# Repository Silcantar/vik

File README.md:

# VIK

> **Warning**
> This is a work in progress. It has been tested to be functional, but please consult **sadekbaroudi** in the **#vik** channel of the [fingerpunch discord server](https://fingerpunch.xyz/discord) if you'd like to design a keyboard or module.

> **Note**
> **To see the list of known supported keyboards and modules, go to [this section](#known-list-of-vik-certifications) at the bottom of the readme**

> **Note**
> Please be aware that for keyboard pcbs, VIK assumes that it's running at 3.3v logic levels. This is easily achieved by using a RP2040. If you are using a 5v controller, it is the keyboard's responsibility to level shift before going to the VIK module. See the [Microcontroller selection](#microcontroller-selection) section below

## License

**The licensing for VIK works as follows:**
The main `LICENSE.md` in the git repository root directory applies to the whole repo, except where there is a `LICENSE.md` in the sub-folder. In that case, that `LICENSE.md` is then applied recursively until there is another `LICENSE.md` in any of its subdirectories (if any).

## Overview

VIK is a standard for a data interface between printed circuit boards. It is intended to provide modularity between a mechanical keyboard pcb and additional features. The main pcb can have a controller and a switch matrix, while the modules can provide additional features.

The standard specifies the following:
1. The type of connector
2. The signals mapped to each pin on the connector
3. The type of cable
4. (optional) The size of the module pcb and mounting hole locations
5. Inclusion of the VIK logo on the PCB

> **Note**
> Adding support for VIK is as simple as adding a symbol and footprint, provided in this repository, followed by some basic wiring. If you want to jump straight to the guide to do this using Kicad, go to [Implementation with Kicad](#implementation-with-kicad)

## Renders

Keyboard with VIK certification using the keyboard footprint

Module with VIK certification using the module footprint

### What value does this bring?

#### Consoldiates efforts for feature design

In a community full of talented people doing lots of innovation, we are seeing a plethora of new options for keyboard layout configurations, features, etc. With all this innovation, we're doing very little to share our efforts.

For example, if one person invests in adding support for a trackball with a scroll wheel, others have to identify how to do that, and add support for their keyboard design.

#### Ease of upgrades

With VIK support, upgrading your features is as simple as getting a new VIK module, and swapping it out.

Let's say you built a keyboard with an integrated trackpad, and you love it. Months after setting it up, you realize that you'd love to have a trackball and haptic feedback. Now you need to design a new pcb (or find someone who has) with the features you'd like. Most people don't know how, or don't want to put forth this effort, so they will settle for their current configuration. With much less effort, you can create a new VIK module, assemble it, and connect to your existing keyboard.

#### One feature for many keyboard layouts

One of the biggest challengs I find, is that a keyboard may have some really excellent features, but I really don't like the key layout. In that case, I won't be interested in the keyboard, despite wanting the features.

Provided that keyboard designers adopt the VIK standard on the main keyboard pcb, the modules are usable on any of those keyboards. So, you can design or find a keyboard that has your preferred layout, and then add the features that you like. True customizability for the exact keyboard you want to use.

## Specifications

There are two things that must be implemented for this to be successful. The keyboard pcb must support the VIK interface, and the module pcb must support the VIK interface

### Connector

The required connector is a FPC 12 pin 0.5mm pitch connector. It should be available on both the keyboard pcb and the module pcb.

#### JLCPCB part selection tips

I've received feedback that the recommended part number `C479750` for the fpc connector (`vik-{keyboard|module}-connector-horizontal`) is frequently out of stock. Fortunately, there are many equivalent parts that line up identically to this one.

To find an equivalent, I generally just search for "12p 0.5mm fpc clamshell". Then I pick one that looks identical to `C479750`. During PCBA part placement, go into 3D mode and adjust the view to make sure the pads line up nicely with the connectors. An example of an alternative part number is `C2906115`.

### Cable

The cable should be a 12 pin 0.5mm pitch FPC Type A cable (leads are exposed on the same side).

The specs below state that you must invert the connector pin order between the keyboard and the module, which means Type A is required.

### Interface

The interface includes the following signals:
* 3.3V
* GND
* SDA
* SCL
* RGB Data Out
* Vout
* Digital/Analog GPIO/CS 1
* MOSI
* Digital/Analog GPIO/CS 2
* Digital/Analog GPIO/CS 3
* MISO
* SCLK

The order specified above is the order they should be used on the FPC connector on the **keyboard side**, pins 1 through 12. For the module pcbs, they should be inverted, since the cable will automatically invert the order when connected. If you use the VIK Kicad symbols and footprints, this is managed for you. See the [Implementation with Kicad](#implementation-with-Kicad) section below

### VIK logo

So long as you adhere to the specs above, you can consider your keyboard pcb or module VIK enabled. The last thing you do before publishing or manufacturing your PCB is to include the VIK logo.

There are a collection of logos you can use in the kicad/vik.pretty directory of this repository, all prefixed with `vik-logo`. For instance, you could take the pre-made kicad footprints and include them on your pcb. If you aren't using kicad, there is a dxf and svg you can use as well.

## Module PCB shape and mounting

This is optional, but highly recommended. By adhereing to a standard size and mounting, this will allow others to design keyboard pcbs and/or cases that will support mounting a variety of modules.

There are two specs, a small and large pcb.

**All mounting holes should fit M2 screws**

### Small PCB

Size: less than 25mm by 42mm

Mounting: 2 mounting holes

### Large PCB

Size: less than 65mm by 65mm

Mounting: 4 mounting holes

The mounting holes should 44.5mm apart in a square, centered around the center of the pcb. Alternatively, you can place these mounting holes evenly distributed around a 63mm circle, also centered around the center of the pcb.

### Module mounting Kicad footprints

There are two mounting footprints, found in the vik.pretty footprints folder:
* vik-module-mounting-small
* vik-module-mounting-large

You can use these for one of two purposes:
1) When creating a module, use the footprint to ensure that your module pcb has the correct mounting locations
2) When creating a keyboard, use the footprint to position where you'd like to mount a module pcb

You can use the Mounting Hole symbol in the schematic, and associate one of the footprints as shown below:

## Implementation with Kicad

Given Kicad's popularity, I've made it (hopefully) very convenient to implement VIK on the keyboard and module side.

### Add symbols and footprints to your Kicad project

1. Clone this repository to your local machine
2. Add the VIK symbol library your project
3. Add the VIK footprint library to your project

Please note that the path in the screenshots won't be the same as yours. It should be:
`{PATH TO CLONE OF THIS REPO}/kicad/vik.kicad_sym`
and
`{PATH TO CLONE OF THIS REPO}/kicad/vik.pretty`

### Kicad keyboard connector

1. Add a new symbol in the schematic, and select the `vik-keyboard-connector`
2. Connect all the signals as specified
3. Associate with the type of footprint you'd like to use (all of the VIK examples use the horizontal connector footprint). Given you are making a keyboard connector, be sure to use the ones that have the word keyboard in them. See the image below for an example.
4. Update your PCB from the schematic and wire it up!

#### Adding the keyboard connector symbol

#### Assigning the keyboard connector footprint

#### Example schematic for keyboard connector

#### Example wiring for keyboard connector

### Kicad module connector

1. Add a new symbol in the schematic, and select the `vik-module-connector`
2. Connect all the signals as specified
3. Associate with the type of footprint you'd like to use (all of the VIK examples use the horizontal connector footprint). Given you are making a module connector, be sure to use the ones that have the word module in them. See the image below for an example.
4. Update your PCB from the schematic and wire it up!

#### Adding the module connector symbol

#### Assigning the module connector footprint

#### Example schematic for module connector

#### Example wiring for module connector

## Schematic design guide

Assuming you already have the VIK symbols and footprints included in your schematic, you will need to wire them according to the specs. Let's walk through each signal, and review how to wire. I'll break this into two parts, one for the keyboard design, and one for the module design.

### Keyboard schematic guide

First and foremost, it's very important that the keyboard have everything set up correctly. Given it's the one supplying the signals to the module, you want to be fully compatible with as many modules as possible.

Here is each signal, and an overview of how to wire it.

**3.3V**

This one is fairly straight forward in the sense that you just need to supply 3.3v. That said, there are controllers out there that do not include it natively. Please review the [Microcontroller selection](#Microcontroller-selection) section below for details.

On wireless microcontrollers, this should be connected directly to BAT+ or to the output of a 3.3V voltage regulator. Do not connect it to the switchable VCC pin (on Nice!Nano or nRFmicro) or to VUSB (on Seeed XIAO nRF52840).

**GND**

Connect ground to this pin.

**SDA**

Microcontrollers usually have more than one set of I2C signals. On dev boards like the [Helios](https://github.com/0xCB-dev/0xCB-Helios) or [Elite-Pi](https://docs.keeb.io/elite-pi-guide), it's as simple as wiring the SDA pin to the corresponding SDA pin on the VIK connector.

nRF52840-based controllers like Nice!Nano, nRFmicro, Seeed XIAO nRF52840, and others have both high- and low-frequency IO pins. SPI and I2C pins should be located *only* on high-frequency pins.

**SCL**

This is the exact same as described for SDA, but using SCL instead.

**RGB Data Out**

If you don't have RGB leds on your keyboard, this can be any digital GPIO. Just pick any data signal, and route it to the RGB pin on the VIK connector.

If you are using RGB leds, you'll want to do two things:
1. Wire the data out from the last LED to the RGB pin on the VIK connector
2. Connect from the controller LED data pin to the VIK connector, but put an open jumper in the middle. The nice thing about this is that it allows the end user to still use the LED feature on a module without necessarily having the LEDs assembled on their keyboard.

**Vout**

`Vout` is a 5 or 3.3 volt power pin intended for supplying higher-power-consumption components like LEDs or screens.

For wired keyboards, `Vout` should usually be connected to the raw 5V provided by the USB connection. If you are using an RP2040 controller board, be aware that the `VCC` pin is 3.3V. For 5V, connect to the `RAW` or `VBUS` output of the controller. On all RP2040-based controllers that I'm aware of as of this writing, this is the top right pin (please double check this before you wire it up).

For example, on the elite-pi:

Connecting `Vout` is a bit more complicated for battery-powered wireless keyboards. Since most LiPo batteries only provide around 3.7 volts, these keyboards only have 5-volt power available when plugged in. Depending on the microcontroller board and battery you are using, you have several options. The microcontroller board determines the type of power-saving options available. However, if you have a large battery power-saving might not be necessary to achieve acceptable battery life.

- **Nice!Nano, nRFmicro, or similar**
    - For lower power consumption: these boards provide a switchable power output (`VCC`). `Vout` may be connected to this if you want to be able to switch off high-power components.

- **Seeed XIAO nRF52840 or similar**
    - For lower power consumption: `VUSB` is only powered on when the keyboard is plugged in via USB. High-power components will be powered off when USB is unplugged.

- **Lemon Wireless**
    - Connect `Vout` to `VRGB`.

- **Integrated or other microcontrollers**
    - You will have to investigate what options are available.

- **For any microcontroller**
    - For higher power consumption: connect `Vout` to `RAW` or `BAT+`. High-power components will be powered on whenever the keyboard power switch is on. Don't go this route on a keyboard that lacks a power switch.
    - You may integrate a power cutoff circuit into the keyboard PCB. See [nRFmicro](https://github.com/joric/nrfmicro) or [Nice!Nano](https://nicekeyboards.com/docs/nice-nano/pinout-schematic) schematics for examples.
    - If you don't expect your keyboard to need high-power modules, you may leave `Vout` disconnected. Be aware that this limits the options of your users however.

**Digital/Analog GPIO 1/SPI CS1**

Similar to the `RGB Data Out`, you can select any pin, but it should support both digital and analog. Below is an example of the Elite-Pi, highlighting its pins that support both.

This pin may also be used by modules for selecting an SPI device.

**MOSI**

Similar to I2C, SPI has predefined locations on most controllers. If doing an integrated controller, please refer to the datasheet to determine the correct pins.

That said, on dev controllers like the [Helios](https://github.com/0xCB-dev/0xCB-Helios) or [Elite-Pi](https://docs.keeb.io/elite-pi-guide), they are standard locations. See the image below. You can wire the 4 SPI pins as shown.

nRF52840-based controllers like Nice!Nano, nRFmicro, Seeed XIAO nRF52840, and others have both high- and low-frequency IO pins. SPI and I2C pins should be located *only* on high-frequency pins.

**Digital/Analog GPIO 2/SPI CS2**

Same as `Digital/Analog GPIO 1`, but this should be a second independent GPIO or CS of the same specifications.

**Digital/Analog GPIO 3/SPI CS3**

Same as `Digital/Analog GPIO 1`, but this should be a third independent GPIO or CS of the same specifications.

**MISO**

No additional info beyond the `MOSI` section above. Same course of action, but for the MISO signal.

**SCLK**

No additional info beyond the `MOSI` section above. Same course of action, but for the SCLK signal.

### Module schematic guide

There aren't any major considerations for the schematic for the module. Everything on the connector is an input, so you can choose what to do with them.

That said, please note that using the I2C or SPI pins for anything **other than I2C or SPI** will break on keyboards that use those signals on the main board. So, please avoid doing so if you care about maximizing compatibility.

## Design guidelines and recommendations

### Reference designs

For the keyboard side, I created a keyboard called [vulpes minora](http://github.com/sadekbaroudi/vulpes-minora). This keyboard has been manufactured and tested to work with VIK modules.

For the module side, please see the pcb directory in this repository. Each subdirectory within it has a module that you can review to see how these are implemented.

### I2C guidelines

#### Keyboard pcb

As mentioned above, the responsibility of using pull up resistors is on the VIK modules. This may cause challenges for a few reasons. You may want (or need) to use I2C on the main keyboard PCB, which means you need to use pull up resistors. If this is the case, please provide instructions to inform the users that when using VIK modules, they will need to remove (or not place) the pull up resistor on the keyboard.

#### Module pcb

When designing a module, please ensure that you include pull up resistors, since the guidelines state that the keyboard pcb is not responsible for it.

### Microcontroller selection

If you are designing a keyboard pcb that uses a dev board as a controller (e.g. pro micro, elite-c, stemcell, etc), you should consider that the VIK specs calls for 3.3V and 5V. Given these controllers operate on 5V and don't provide 3.3V, you won't be able to use them for VIK compatibility without additonal circuitry to convert 5V to 3.3V.

**As described at the top of the README in the note, the keyboard pcb should run at at 3.3v logic levels. The simplest option is to use a RP2040 based development board. For integrated controllers, either use a controller that already runs at 3.3v logic, or level shift the GPIO before going into the VIK connector.**

Some options include:
1. Support only RP2040 based controllers (e.g. splinky, elite-pi, helios), where VCC is 3.3V, and the RAW pin provides 5V
2. Support other 5V controllers, and use something like an LDO to convert 5V to 3.3V for the VIK 3.3V signal and GPIO signals
3. Anything you want, as long as you can provide 5V and 3.3V (both power and 3.3v gpio logic levels)

The vulpes minora is an example of point number 1 above.

## VIK certification

In order to be VIK certified, you should be compliant with everything above, and have your keyboard or module reviewed. Upon review, the reviewer will make a card for your pcb, as explained below.

### VIK keyboard certification card

#### Descriptions

* **FPC connector:** has the correct FPC connector with the right pinout, and is wired to specificaton. See the connectors in the kicad/vik.pretty directory
* **Breakout pins:** includes breakout pins using the [VIK breakout pin footprint](https://github.com/sadekbaroudi/vik/blob/master/kicad/vik.pretty/vik-keyboard-throughole.kicad_mod), or has through holes for all the signals. This allows easy access to all the signals. Also, the footprint is compatible with a [hand solderable FPC breakout board](https://www.amazon.com/uxcell-Converter-Couple-Extend-Adapter/dp/B07RVD1J1K).
* **Supplies: Vout** supplies Vout (5V or VBAT)
* **Supplies: SPI** supplies SPI signals, including MISO, MOSI, SCLK, and at least one GPIO/CS
* **Supplies: I2C:** supplies I2C, including SDA and SCL
* **I2C on main PCB:** Does the main PCB use any I2C already. Valid responses are `yes` or `no`. If this is true, the `I2C pull ups` field must have a value
* **I2C pull ups:** I2C pull up resistor value, :x: if no pull ups on the main pcb, or resistor value if present
* **Supplies: RGB:** supplies RGB data out
* **Supplies: Extra GPIO/CS 1:** supplies the extra GPIO, response will be one of: (**:x: | Digital Only | Analog/Digital**)
* **Supplies: Extra GPIO/CS 2:** supplies the extra GPIO, response will be one of: (**:x: | Digital Only | Analog/Digital**)
* **Supplies: Extra GPIO/CS 3:** supplies the extra GPIO, response will be one of: (**:x: | Digital Only | Analog/Digital**)

#### Keyboard sample cards

Example of a failing card:

| Category                    | Classification          | Response           |
| --------------------------- | ----------------------- | ------------------ |
| FPC connector               | Required                | :heavy_check_mark: |
| Breakout pins               | Recommended             | :x:                |
| Supplies: Vout              | Recommended             | :x:                |
| Supplies: SPI               | Required                | :heavy_check_mark: |
| Supplies: I2C               | Required                | :heavy_check_mark: |
| I2C on main PCB             | Discouraged             | yes                |
| I2C pull ups                | Informative             | 2.2kΩ              |
| Supplies: RGB               | Required                | :x:                |
| Supplies: Extra GPIO/CS 1   | Required                | :x:                |
| Supplies: Extra GPIO/CS 2   | Required                | :x:                |
| Supplies: Extra GPIO/CS 3   | Required                | :x:                |

A "perfect" keyboard card would look like this:

| Category                    | Classification          | Response           |
| --------------------------- | ----------------------- | ------------------ |
| FPC connector               | Required                | :heavy_check_mark: |
| Breakout pins               | Recommended             | :heavy_check_mark: |
| Supplies: Vout              | Recommended             | :heavy_check_mark: |
| Supplies: SPI               | Required                | :heavy_check_mark: |
| Supplies: I2C               | Required                | :heavy_check_mark: |
| I2C on main PCB             | Discouraged             | no                 |
| I2C pull ups                | Informative             | N/A                |
| Supplies: RGB               | Required                | :heavy_check_mark: |
| Supplies: Extra GPIO/CS 1   | Required                | Analog/Digital     |
| Supplies: Extra GPIO/CS 2   | Required                | Analog/Digital     |
| Supplies: Extra GPIO/CS 3   | Required                | Analog/Digital     |

### VIK module certification card

#### Descriptions

* **FPC connector:** has the correct FPC connector with the right pinout, and is wired to specificaton. See the connectors in the kicad/vik.pretty directory
* **Breakout pins:** includes breakout pins using the [VIK breakout pin footprint](https://github.com/sadekbaroudi/vik/blob/master/kicad/vik.pretty/vik-keyboard-throughole.kicad_mod), or has through holes for all the signals. This allows easy access to all the signals. Also, the footprint is compatible with a [hand solderable FPC breakout board](https://www.amazon.com/uxcell-Converter-Couple-Extend-Adapter/dp/B07RVD1J1K).
* **Uses: Vout** the module uses the Vout pin to power components.
* **Uses: SPI:** the module is utilizing SPI
* **SPI used for SPI only:** if you are using any of the SPI gpio for any purpose other than SPI, this will remain unchecked. This means that keyboard pcbs that use SPI will be incompatible with this module.
* **Uses: I2C:**
* **I2C used for I2C only:** if you are using any of the I2C gpio for any purpose other than I2C, this will remain unchecked. This means that keyboard pcbs that use I2C will be incompatible with this module.
* **I2C pull ups:** I2C pull up resistor value, if applicable. These are only required if I2C is being used on the module.
* **Uses: RGB:** uses RGB data out
* **Uses: Extra GPIO 1:** uses the extra GPIO/CS, response will be one of: (**:x: | Digital Only | Analog/Digital | CS**)
* **Uses: Extra GPIO 2:** uses the extra GPIO/CS, response will be one of: (**:x: | Digital Only | Analog/Digital | CS**)
* **Uses: Extra GPIO 3:** uses the extra GPIO/CS, response will be one of: (**:x: | Digital Only | Analog/Digital | CS**)
* **Standard PCB Size/Mount:** adheres to standard module size and mounts, responses will be one of: (**:x: | Small | Large**)

#### Module sample card

General example:

| Category                | Classification          | Response           |
| ----------------------- | ----------------------- | ------------------ |
| FPC connector           | Required                | :heavy_check_mark: |
| Breakout pins           | Recommended             | :x:                |
| Uses: Vout              | Optional                | :x:
| Uses: SPI               | Optional                | :heavy_check_mark: |
| SPI used for SPI only   | Strongly recommended    | :heavy_check_mark: |
| Uses: I2C               | Optional                | :heavy_check_mark: |
| I2C used for I2C only   | Strongly Recommended    | :heavy_check_mark: |
| I2C pull ups            | Required*               | 4.7kΩ              |
| Uses: RGB               | Optional                | :x:                |
| Uses: Extra GPIO/CS 1   | Optional                | :x:                |
| Uses: Extra GPIO/CS 2   | Optional                | :x:                |
| Uses: Extra GPIO/CS 3   | Optional                | :x:                |
| Standard PCB Size/Mount | Strongly recommended    | Large              |

## Known list of VIK certifications

### Controllers

| Name                                                                                                     | GPIO (excluding VIK connector) | Status                              | Open source or Commercial    | Creator                                           |
| -------------------------------------------------------------------------------------------------------- | ------------------------------ | ----------------------------------- | ---------------------------- | ------------------------------------------------- |
| [svlinky](https://github.com/sadekbaroudi/svlinky/)                                                      | 18                             | Complete                            | Open source                  | [Sadek Baroudi](https://github.com/sadekbaroudi/) |
| [xivik](https://fingerpunch.xyz/product/xivik/)                                                          | 11                             | Complete                            | Commercial                   | [Sadek Baroudi](https://github.com/sadekbaroudi/) |
| [lemon-microcontroller](https://github.com/rianadon/Cosmos-Keyboard-PCBs)                                | 19                             | Complete                            | Open Source / Commercial     | [rianadon](https://github.com/rianadon/)          |
| [lemon-wireless](https://github.com/rianadon/Cosmos-Keyboard-PCBs)                                       | 15                             | Complete                            | Open Source / Commercial     | [rianadon](https://github.com/rianadon/)          |

### Keyboards

| Name                                                                                                                                                             | Keys  | Style   | Status                              | Open source or Commercial    | Creator                                                             |
| ---------------------------------------------------------------------------------------------------------------------------------------------------------------- | ----- | ------- | ----------------------------------- | ---------------------------- | ------------------------------------------------------------------- |
| [vulpes minora](https://github.com/sadekbaroudi/vulpes-minora/)                                                                                                  | 36    | Split   | Complete                            | Open source                  | [Sadek Baroudi](https://github.com/sadekbaroudi/)                   |
| [ximi](https://fingerpunch.xyz/product/ximi/)                                                                                                                    | 36/42 | Split   | Complete                            | Commercial                   | [Sadek Baroudi](https://github.com/sadekbaroudi/)                   |
| [stront](https://github.com/zzeneg/stront/)                                                                                                                      | 38    | Split   | Partial support (see stront readme) | Open source                  | [zzeneg](https://github.com/zzeneg/)                                |
| [Honeydew](https://github.com/Ariamelon/Honeydew/)                                                                                                               | 63    | Unibody | Work in progress                    | Open source                  | [Ariamelon](https://github.com/Ariamelon/Honeydew/)                 |
| [Benboard](https://github.com/ben-labs-ltd/benboard) / [Benboard - commercial](https://ben-labs.co.uk/)                                                          | 42    | Split   | Work in progress                    | Commercial / Open source     | [Ben](https://github.com/ben-labs-ltd/)                             |
| [DragonFruit](https://github.com/protieusz/DragonFruit)                                                                                                          | 38    | Unibody | Complete                            | Open source                  | [protieusz](https://github.com/protieusz/)                          |
| [ZodiarkPi (product)](https://www.splitlogic.xyz/shop/splitlogic/p/zodiarkpi) [(cert)](https://github.com/sadekbaroudi/vik/tree/master/pcb/splitlogic/)          | 68    | Split   | Complete                            | Commercial                   | [Aleblazer](https://github.com/aleblazer/)                          |
| [ZodiPact (product)](https://www.splitlogic.xyz/shop/splitlogic/p/zodipact-pcb-kit) [(cert)](https://github.com/sadekbaroudi/vik/tree/master/pcb/splitlogic/)    | 68    | Split   | Complete                            | Commercial                   | [Aleblazer](https://github.com/aleblazer/)                          |
| peacock trackpad macropad/controller [(project)](https://github.com/george-norton/peacock) [(cert)](https://github.com/sadekbaroudi/vik/tree/master/pcb/peacock) | 5     | Unibody | Complete                         | Open source                  | [George Norton](https://github.com/george-norton)                   |
| Dilemma [(product)](https://bastardkb.com/dilemma/) [(project)](https://github.com/Bastardkb/Dilemma/tree/features/dilemma_3x0/3x5_3) [(cert)](https://github.com/sadekbaroudi/vik/tree/master/pcb/dilemma)   | 36    | Split | Complete                         | Commercial / Open source                  | [Quentin Lebastard](https://github.com/Bastardkb)                   |

### Modules

| Name                                                                                               | Function                                             | Status                              | Open source or Commercial    | Creator                                             |
|----------------------------------------------------------------------------------------------------| -------------------------------------------          | ----------------------------------- | ---------------------------- |-----------------------------------------------------|
| [haptic](https://github.com/sadekbaroudi/vik/tree/master/pcb/haptic/)                              | Pimoroni Haptic Feedback                             | Complete                            | Open source                  | [Sadek Baroudi](https://github.com/sadekbaroudi/)   |
| [haptic-drv2605l](https://github.com/sadekbaroudi/vik/tree/master/pcb/haptic-drv2605l/)            | Haptic Feedback using DRV2605L controller            | Complete                            | Open source                  | [zzeneg](https://github.com/zzeneg/)                |
| [per56-cirque-leds](https://github.com/sadekbaroudi/vik/tree/master/pcb/per56-cirque-leds/)        | Scroll ring, cirque trackpad, RGB LEDs               | Complete                            | Open source                  | [Sadek Baroudi](https://github.com/sadekbaroudi/)   |
| [per56-pmw3360-leds](https://github.com/sadekbaroudi/vik/tree/master/pcb/per56-pmw3360-leds/)      | Scroll ring, trackball, RGB LEDs                     | Complete                            | Open source                  | [Sadek Baroudi](https://github.com/sadekbaroudi/)   |
| [per56-pmw3360-cirque-leds (Kiwano)](https://github.com/Ariamelon/Kiwano/)                         | Scroll ring, cirque or trackball, RGB LEDs           | Complete                            | Open source                  | [Ariamelon](https://github.com/Ariamelon/Honeydew/) |
| [pmw3360](https://github.com/sadekbaroudi/vik/tree/master/pcb/pmw3360/)                            | Trackball                                            | Complete                            | Open source                  | [Sadek Baroudi](https://github.com/sadekbaroudi/)   |
| [ssd1351 (Crenshaw)](https://github.com/Ariamelon/Crenshaw/)                                       | Color display                                        | Complete                            | Open source                  | [Ariamelon](https://github.com/Ariamelon/Honeydew/) |
| [weact-st7735](https://github.com/sadekbaroudi/vik/tree/master/pcb/weact-st7735/)                  | WeAct ST7735 1.8" color display adapter              | Complete                            | Open source                  | [Sadek Baroudi](https://github.com/sadekbaroudi/)   |
| [gc9a01](https://github.com/sadekbaroudi/vik/tree/master/pcb/gc9a01/)                              | gc9a01 round display breakout adapter                | Complete                            | Open source                  | [Sadek Baroudi](https://github.com/sadekbaroudi/)   |
| [waveshare-22224](https://github.com/sadekbaroudi/vik/tree/master/pcb/waveshare-22224/)            | waveshare 22224 1.47" display adapter                | Complete                            | Open source                  | [Sadek Baroudi](https://github.com/sadekbaroudi/)   |
| [azoteq-tps](https://github.com/sadekbaroudi/vik/tree/master/pcb/azoteq-tps/)                      | Azoteq Proxsense TPS43 and TPS65                     | Complete                            | Open source                  | [Sadek Baroudi](https://github.com/sadekbaroudi/)   |
| [trackpoint](https://github.com/sadekbaroudi/vik/tree/master/pcb/trackpoint-2-piece/)              | Trackpoint 2 piece adapter                           | Complete                            | Open source                  | [Sadek Baroudi](https://github.com/sadekbaroudi/)   |
| [ec11-evqwgd001](https://github.com/sadekbaroudi/vik/tree/master/pcb/ec11-evqwgd001/)              | EC11 and EVQWDG001 with RGB leds                     | Complete                            | Open source                  | [Sadek Baroudi](https://github.com/sadekbaroudi/)   |
| [joysticks](https://github.com/sadekbaroudi/vik/tree/master/pcb/joysticks/)                        | adafruit 2765, sparkfun 9032, joycon                 | Complete                            | Open source                  | [Sadek Baroudi](https://github.com/sadekbaroudi/)   |
| [vik-playground](https://github.com/sadekbaroudi/vik/tree/master/pcb/vik-playground/)              | module for prototyping and testing VIK               | Complete                            | Open source                  | [Sadek Baroudi](https://github.com/sadekbaroudi/)   |
| [vik-universal](https://github.com/sadekbaroudi/vik/tree/master/pcb/vik-universal/)                | for connecting any through hole board w/VIK          | Complete                            | Open source                  | [Sadek Baroudi](https://github.com/sadekbaroudi/)   |
| [ili9341v](https://github.com/sadekbaroudi/vik/tree/master/pcb/ili9341v/)                          | Display with capacitive touch and SD card            | Complete                            | Open source                  | [Sadek Baroudi](https://github.com/sadekbaroudi/)   |
| [nice!view](https://github.com/sadekbaroudi/vik/tree/master/pcb/niceview/)                         | nice!view display                                    | Untested                            | Open source                  | [Sadek Baroudi](https://github.com/sadekbaroudi/)   |
| [vik-display-adapter](https://github.com/zzeneg/vik-display-adapter)                               | various display adapters in different sizes          | Complete                            | Open source                  | [zzeneg](https://github.com/zzeneg/)                |
| [shift-register-spi-breakout-pcb](https://github.com/christrotter/shift-register-spi-breakout-pcb) | dual shift register breakout for extended key matrix | Untested                            | Open source                  | [Chris Trotter](https://github.com/christrotter/)   |
| [pmw3610](https://github.com/sadekbaroudi/vik/tree/master/pcb/pmw3610/)                            | Trackball (for wireless boards)                      | Complete                            | Open source                  | [Sadek Baroudi](https://github.com/sadekbaroudi/)   |
| [pmw3610-xs](https://github.com/sadekbaroudi/vik/tree/master/pcb/pmw3610-xs/)                      | Trackball (for wireless boards)                      | Complete                            | Open source                  | [Sadek Baroudi](https://github.com/sadekbaroudi/)   |
| [pmw3610-xxs](https://github.com/sadekbaroudi/vik/tree/master/pcb/pmw3610-xxs/)                    | Trackball (for wireless boards)                      | Complete                            | Open source                  | [ykz89](https://github.com/ykz89/)                  |
| [vikropad](https://github.com/sadekbaroudi/vik/tree/master/pcb/vikropad/)                          | Macropad (18 key) with 2x 5 way switches             | Complete                            | Open source                  | [Sadek Baroudi](https://github.com/sadekbaroudi/)   |
| [solenoid-1](https://github.com/sadekbaroudi/vik/tree/master/pcb/solenoid/)                        | Solenoid module using 3.3v or 5v and 1 gpio          | Complete                            | Open source                  | [Sadek Baroudi](https://github.com/sadekbaroudi/)   |
| [solenoid-2](https://github.com/sadekbaroudi/vik/tree/master/pcb/solenoid/)                        | Solenoid module using 5v and 1 gpio                  | Complete                            | Open source                  | [Aleblazer](https://github.com/Aleblazer/)          |
| [peacock trackpad](https://github.com/george-norton/peacock)                                       | Large trackpad module                                | Complete                            | Open source                  | [George Norton](https://github.com/george-norton)   |
| [procyon trackpad](https://github.com/george-norton/procyon)                                       | multi touch trackpad module                          | Complete                            | Open source                  | [George Norton](https://github.com/george-norton)   |
| [vik-splitter](https://github.com/sadekbaroudi/vik/tree/master/pcb/vik-splitter/)                  | module to split one vik in connector to two vik outs | Untested                            | Open source                  | [Sadek Baroudi](https://github.com/sadekbaroudi/)   |

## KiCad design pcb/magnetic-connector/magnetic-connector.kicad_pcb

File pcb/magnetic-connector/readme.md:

# Magnetic Connectors

## Overview

This is a pair of PCBs that adapt a VIK FPC cable to a 12-pin, 2.2mm pitch
magnetic pogo pin connector and back. The pinout of the magnetic connectors is
equivalent to the standard VIK breakout pin layout.

## Fabrication and BOM

For PCB fabrication, you can use the files in the `production` folder.

* `magnetic-connector.zip` - the file used to fabricate the pcb
* `bom.csv` - used for PCBA. You can also use the part numbers in this file to
  look up the exact parts as [lcsc.com](https://lcsc.com)
* `positions.csv` - used for PCBA

Using the 3 files above, this has been tested at [jlcpcb.com](https://jlcpcb.com)

## VIK module certification

| Category                | Classification          | Response           |
| ----------------------- | ----------------------- | ------------------ |
| FPC connector           | Required                | :heavy_check_mark: |
| Breakout pins           | Recommended             | :heavy_check_mark:*|
| Uses: SPI               | Optional                | :x:                |
| SPI used for SPI only   | Strongly recommended    | :x:                |
| Uses: I2C               | Optional                | :x:                |
| I2C used for I2C only   | Strongly Recommended    | :x:                |
| I2C pull ups            | Required                | :x:                |
| Uses: RGB               | Optional                | :x:                |
| Uses: Extra GPIO 1      | Optional                | :x:                |
| Uses: Extra GPIO 2      | Optional                | :x:                |
| Standard PCB Size/Mount | Strongly recommended    | :x:                |

\* If you count the footprint of the magnetic connector.

## PCB images

### horizontal fpc

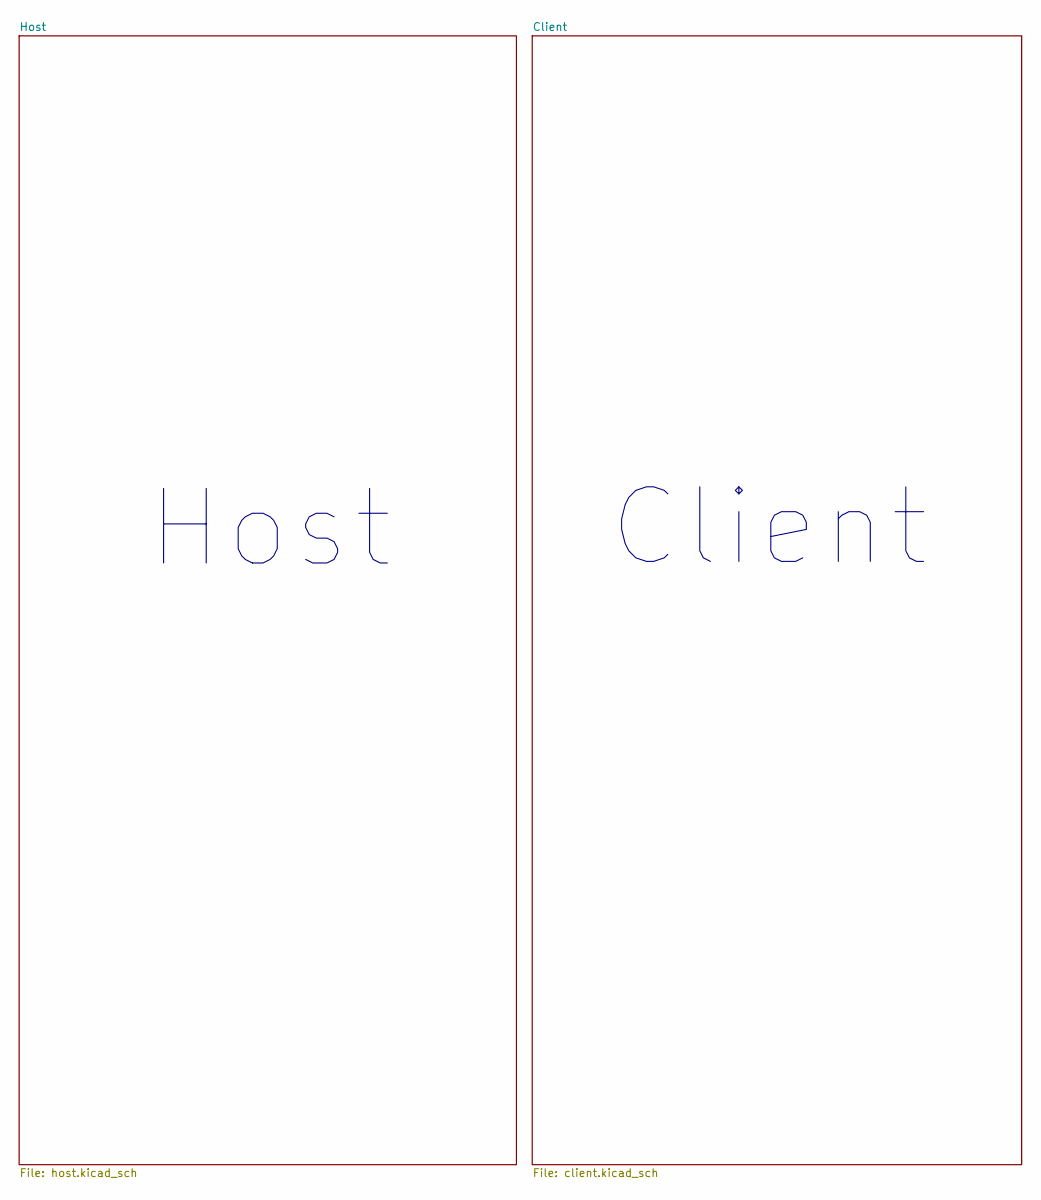
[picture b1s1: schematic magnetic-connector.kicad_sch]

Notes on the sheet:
Host
Client

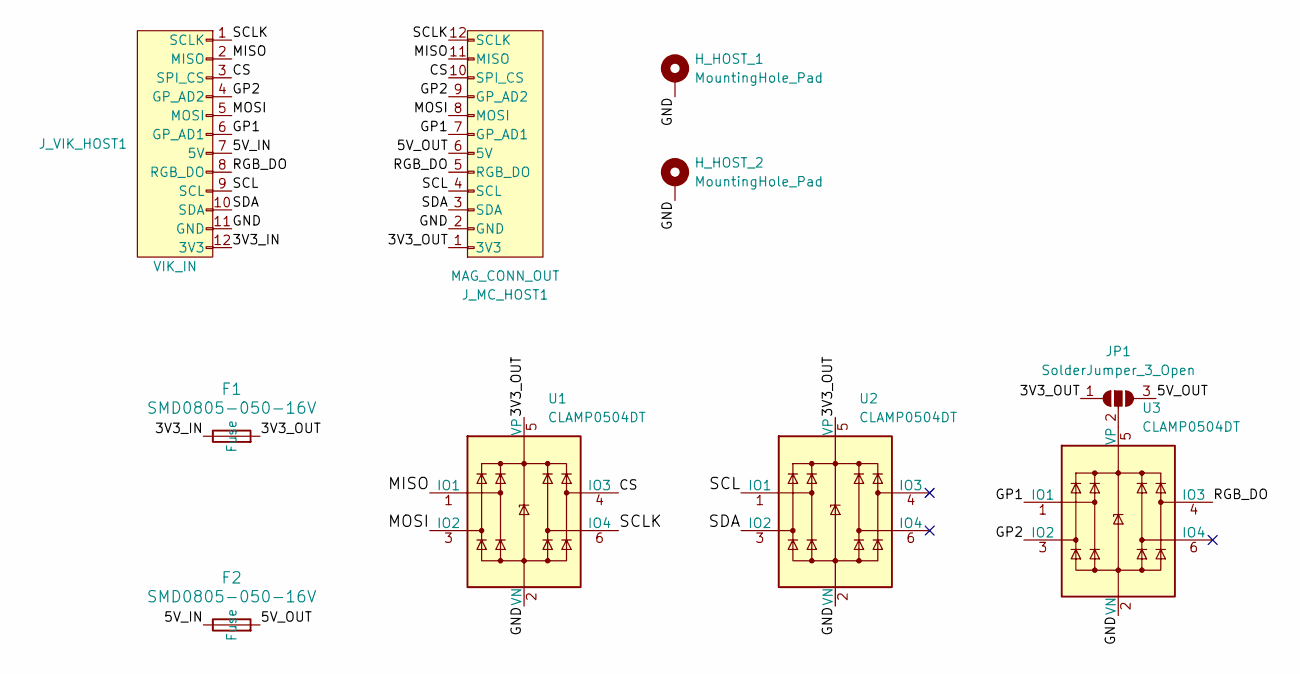
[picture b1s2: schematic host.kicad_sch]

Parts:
F1, F2: SMD0805-050-16V; Fuse_0805_2012Metric; Manufacturer Part Number SMD0805-050-16V; LCSC Part Number C2833485
H_HOST_1, H_HOST_2: MountingHole_Pad; MountingHole_2.2mm_M2_Pad
JP1: SolderJumper_3_Open; SolderJumper-3_P2.0mm_Open_TrianglePad1.0x1.5mm_NumberLabels
J_MC_HOST1: MAG_CONN_OUT; vik-keyboard-throughole-2.2mm
J_VIK_HOST1: VIK_IN; vik-module-connector-horizontal; LCSC C2856799
U1, U2, U3: CLAMP0504DT; SOT-23-6; LCSC C2688137

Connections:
/Host/3V3_IN: F1.1, J_VIK_HOST1.12 (3V3)
/Host/3V3_OUT: F1.2, JP1.1 (A), J_MC_HOST1.1 (3V3), U1.5 (VP), U2.5 (VP)
/Host/5V_IN: F2.1, J_VIK_HOST1.7 (5V)
/Host/5V_OUT: F2.2, JP1.3 (B), J_MC_HOST1.6 (5V)
/Host/CS: J_MC_HOST1.10 (SPI_CS), J_VIK_HOST1.3 (SPI_CS), U1.4 (IO3)
/Host/GND: H_HOST_1.1 (1_1), H_HOST_2.1 (1_1), J_MC_HOST1.2 (GND), J_VIK_HOST1.11 (GND), J_VIK_HOST1.13, J_VIK_HOST1.14, U1.2 (VN), U2.2 (VN), U3.2 (VN)
/Host/GP1: J_MC_HOST1.7 (GP_AD1), J_VIK_HOST1.6 (GP_AD1), U3.1 (IO1)
/Host/GP2: J_MC_HOST1.9 (GP_AD2), J_VIK_HOST1.4 (GP_AD2), U3.3 (IO2)
/Host/MISO: J_MC_HOST1.11 (MISO), J_VIK_HOST1.2 (MISO), U1.1 (IO1)
/Host/MOSI: J_MC_HOST1.8 (MOSI), J_VIK_HOST1.5 (MOSI), U1.3 (IO2)
/Host/RGB_DO: J_MC_HOST1.5 (RGB_DO), J_VIK_HOST1.8 (RGB_DO), U3.4 (IO3)
/Host/SCL: J_MC_HOST1.4 (SCL), J_VIK_HOST1.9 (SCL), U2.1 (IO1)
/Host/SCLK: J_MC_HOST1.12 (SCLK), J_VIK_HOST1.1 (SCLK), U1.6 (IO4)
/Host/SDA: J_MC_HOST1.3 (SDA), J_VIK_HOST1.10 (SDA), U2.3 (IO2)
unnamed: JP1.2 (C), U3.5 (VP)

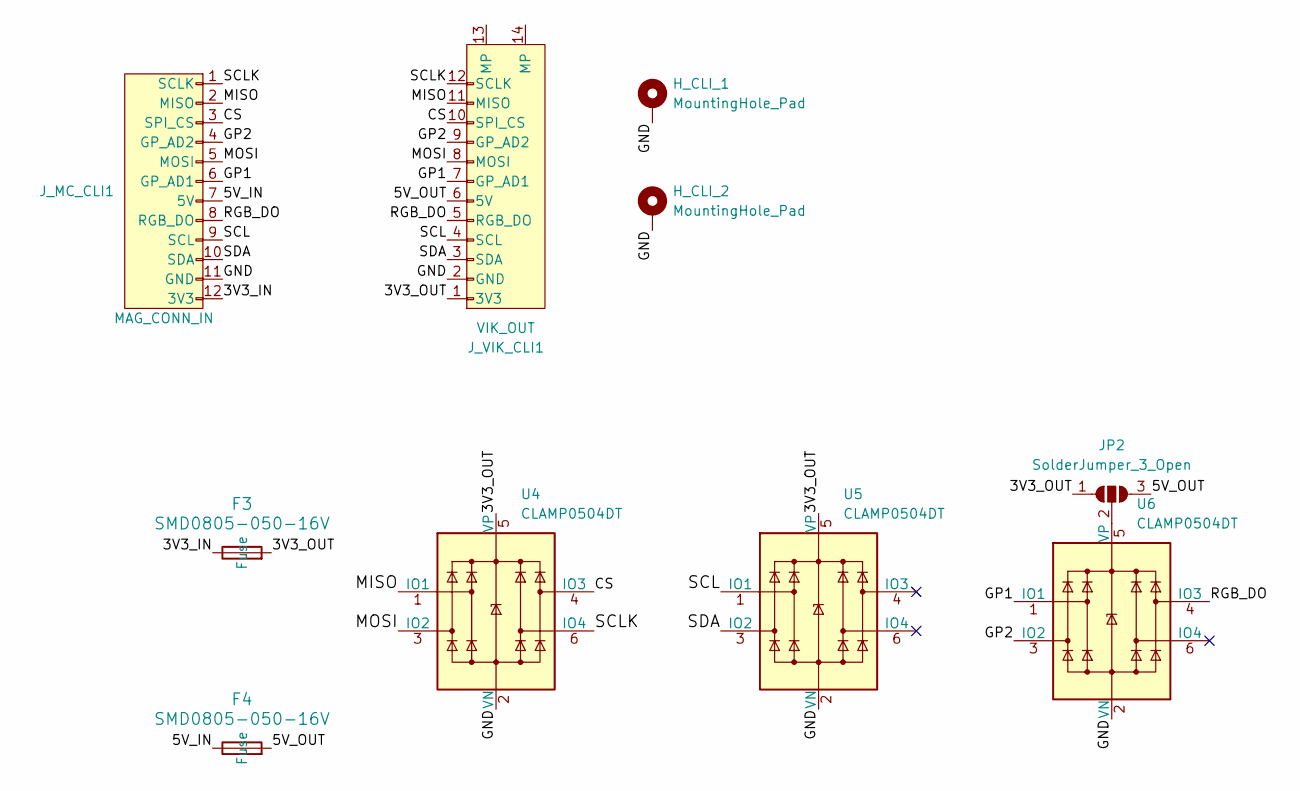
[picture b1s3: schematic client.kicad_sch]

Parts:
F3, F4: SMD0805-050-16V; Fuse_0805_2012Metric; Manufacturer Part Number SMD0805-050-16V; LCSC Part Number C2833485
H_CLI_1, H_CLI_2: MountingHole_Pad; MountingHole_2.2mm_M2_Pad
JP2: SolderJumper_3_Open; SolderJumper-3_P2.0mm_Open_TrianglePad1.0x1.5mm_NumberLabels
J_MC_CLI1: MAG_CONN_IN; vik-module-throughole-2.2mm
J_VIK_CLI1: VIK_OUT; vik-keyboard-connector-horizontal; LCSC C2856799
U4, U5, U6: CLAMP0504DT; SOT-23-6; LCSC C2688137

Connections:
/Client/3V3_IN: F3.1, J_MC_CLI1.12 (3V3)
/Client/3V3_OUT: F3.2, JP2.1 (A), J_VIK_CLI1.1 (3V3), U4.5 (VP), U5.5 (VP)
/Client/5V_IN: F4.1, J_MC_CLI1.7 (5V)
/Client/5V_OUT: F4.2, JP2.3 (B), J_VIK_CLI1.6 (5V)
/Client/CS: J_MC_CLI1.3 (SPI_CS), J_VIK_CLI1.10 (SPI_CS), U4.4 (IO3)
/Client/GND: H_CLI_1.1 (1_1), H_CLI_2.1 (1_1), J_MC_CLI1.11 (GND), J_VIK_CLI1.2 (GND), J_VIK_CLI1.13 (MP), J_VIK_CLI1.14 (MP), U4.2 (VN), U5.2 (VN), U6.2 (VN)
/Client/GP1: J_MC_CLI1.6 (GP_AD1), J_VIK_CLI1.7 (GP_AD1), U6.1 (IO1)
/Client/GP2: J_MC_CLI1.4 (GP_AD2), J_VIK_CLI1.9 (GP_AD2), U6.3 (IO2)
/Client/MISO: J_MC_CLI1.2 (MISO), J_VIK_CLI1.11 (MISO), U4.1 (IO1)
/Client/MOSI: J_MC_CLI1.5 (MOSI), J_VIK_CLI1.8 (MOSI), U4.3 (IO2)
/Client/RGB_DO: J_MC_CLI1.8 (RGB_DO), J_VIK_CLI1.5 (RGB_DO), U6.4 (IO3)
/Client/SCL: J_MC_CLI1.9 (SCL), J_VIK_CLI1.4 (SCL), U5.1 (IO1)
/Client/SCLK: J_MC_CLI1.1 (SCLK), J_VIK_CLI1.12 (SCLK), U4.6 (IO4)
/Client/SDA: J_MC_CLI1.10 (SDA), J_VIK_CLI1.3 (SDA), U5.3 (IO2)
unnamed: JP2.2 (C), U6.5 (VP)

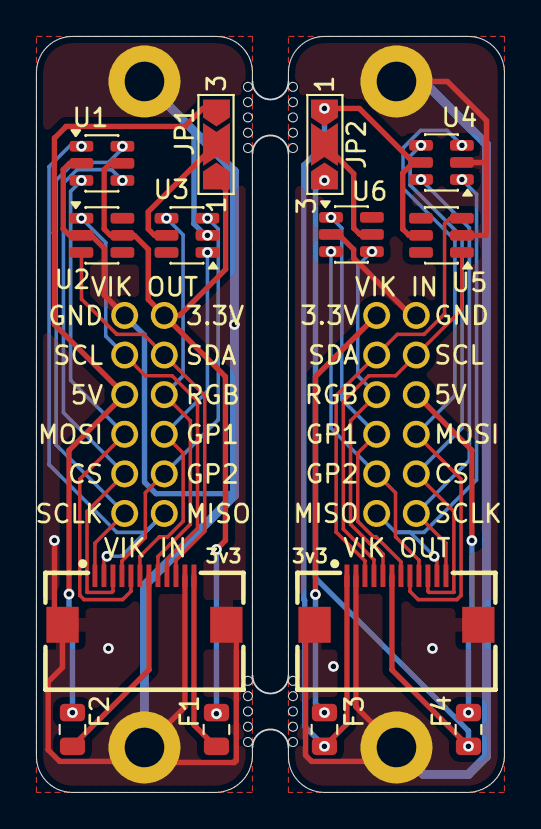
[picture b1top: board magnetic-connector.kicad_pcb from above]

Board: 2 copper layers, 26.0 x 42.0 mm, 20 parts (0 on the bottom side), 30 nets.

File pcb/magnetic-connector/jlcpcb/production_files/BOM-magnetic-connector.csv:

Comment,Designator,Footprint,LCSC,Quantity
CLAMP0504DT,"U1,U2,U3,U4,U5,U6",SOT-23-6,C2688137,6
SMD0805-050-16V,"F1,F2,F3,F4",Fuse_0805_2012Metric,C2833485,4
VIK_IN,J_VIK_HOST1,vik-module-connector-horizontal,C2856799,1
VIK_OUT,J_VIK_CLI1,vik-keyboard-connector-horizontal,C2856799,1
MAG_CONN_IN,J_MC_CLI1,vik-module-throughole-2.2mm,,1
MAG_CONN_OUT,J_MC_HOST1,vik-keyboard-throughole-2.2mm,,1

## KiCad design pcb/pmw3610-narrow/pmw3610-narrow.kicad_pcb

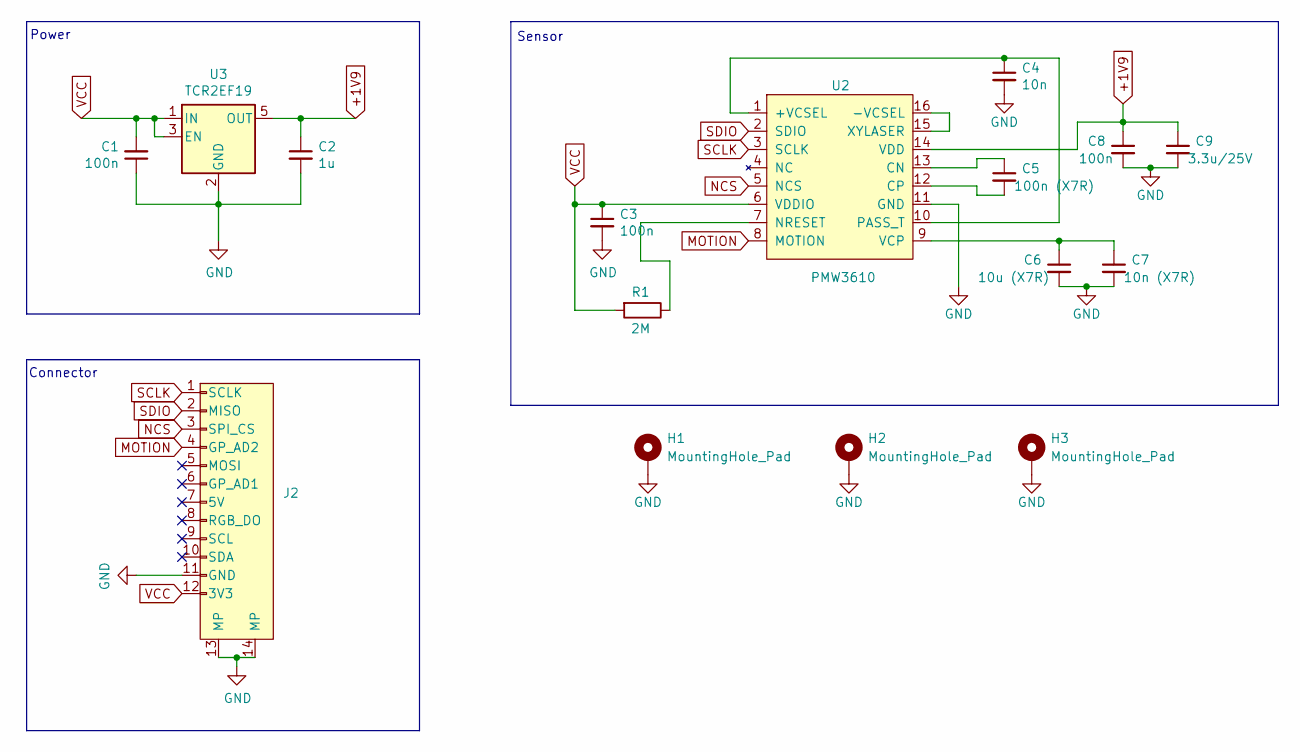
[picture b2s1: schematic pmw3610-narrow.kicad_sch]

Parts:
C1: 100n; C_0805_2012Metric_Pad1.18x1.45mm_HandSolder; LCSC C15849
C2: 1u; C_0805_2012Metric_Pad1.18x1.45mm_HandSolder; LCSC C15849
C3, C8: 100n; C_0805_2012Metric_Pad1.18x1.45mm_HandSolder; LCSC C14663
C4: 10n; C_0805_2012Metric_Pad1.18x1.45mm_HandSolder; LCSC C57112
C5: 100n (X7R); C_0805_2012Metric_Pad1.18x1.45mm_HandSolder; LCSC C14663
C6: 10u (X7R); C_0805_2012Metric_Pad1.18x1.45mm_HandSolder; LCSC C19702
C7: 10n (X7R); C_0805_2012Metric_Pad1.18x1.45mm_HandSolder; LCSC C57112
C9: 3.3u/25V; C_0805_2012Metric_Pad1.18x1.45mm_HandSolder; LCSC C51412
H1, H2, H3: MountingHole_Pad; MountingHole_2.2mm_M2_Pad
J2: vik-module-connector; vik-module-connector-horizontal-mini; LCSC C5213732
R1: 2M; R_0805_2012Metric_Pad1.20x1.40mm_HandSolder; LCSC C2930148
U2: PMW3610; PMW3610DM-SUDU 16Pin
U3: TCR2EF19; SOT-23-5; LCSC C146366

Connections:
+1V9: C2.1, C8.1, C9.1, U2.14 (VDD), U3.5 (OUT)
GND: C1.1, C2.2, C3.2, C4.2, C6.2, C7.2, C8.2, C9.2, H1.1 (1_1), H2.1 (1_1), H3.1 (1_1), J2.11 (GND), J2.13 (MP), J2.14 (MP), U2.11 (GND), U3.2 (GND)
MOTION: J2.4 (GP_AD2), U2.8 (MOTION)
NCS: J2.3 (SPI_CS), U2.5 (NCS)
unnamed: C4.1, U2.1 (+VCSEL), U2.10 (PASS_T)
unnamed: U2.15 (XYLASER), U2.16 (-VCSEL)
unnamed: C5.1, U2.13 (CN)
unnamed: C5.2, U2.12 (CP)
unnamed: R1.1, U2.7 (NRESET)
unnamed: C6.1, C7.1, U2.9 (VCP)
SCLK: J2.1 (SCLK), U2.3 (SCLK)
SDIO: J2.2 (MISO), U2.2 (SDIO)
VCC: C1.2, C3.1, J2.12 (3V3), R1.2, U2.6 (VDDIO), U3.1 (IN), U3.3 (EN)

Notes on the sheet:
Sensor
Connector
Power

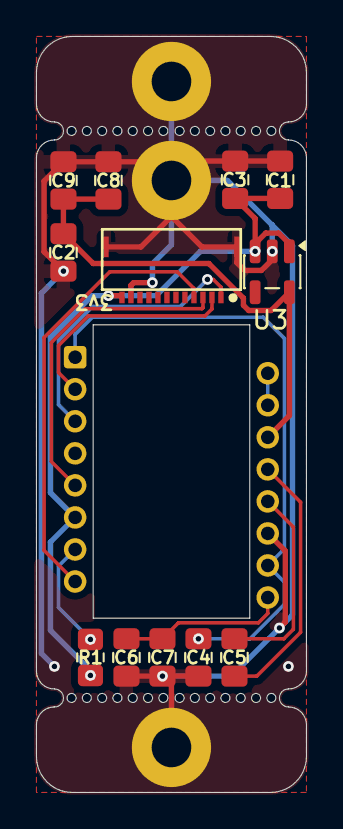
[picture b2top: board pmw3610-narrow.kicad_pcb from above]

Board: 2 copper layers, 15.0 x 42.0 mm, 16 parts (0 on the bottom side), 13 nets.

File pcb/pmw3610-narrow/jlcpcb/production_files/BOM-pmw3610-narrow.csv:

Comment,Designator,Footprint,LCSC,Quantity
100n,"C3,C8",C_0603_1608Metric_Pad1.08x0.95mm_HandSolder,C14663,2
100n (X7R),C5,C_0603_1608Metric_Pad1.08x0.95mm_HandSolder,C14663,1
10n,C4,C_0603_1608Metric_Pad1.08x0.95mm_HandSolder,C57112,1
10n (X7R),C7,C_0603_1608Metric_Pad1.08x0.95mm_HandSolder,C57112,1
10u (X7R),C6,C_0603_1608Metric_Pad1.08x0.95mm_HandSolder,C19702,1
1u,"C1,C2",C_0603_1608Metric_Pad1.08x0.95mm_HandSolder,C15849,2
2M,R1,R_0603_1608Metric_Pad0.98x0.95mm_HandSolder,C2930148,1
3.3u/25V,C9,C_0603_1608Metric_Pad1.08x0.95mm_HandSolder,C51412,1
MG6208T3-18,U1,SOT-23,C22395363,1
vik-module-connector,J2,vik-module-connector-horizontal-mini,C2906115,1

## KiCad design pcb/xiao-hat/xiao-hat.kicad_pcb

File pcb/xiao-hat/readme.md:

# XIAO VIK Hat

## Overview

This is a simple PCB to add a VIK connector to a Seeed XIAO microcontroller
board. It is mainly intended for the nRF52840 XIAO variant but probably works
for the other variants as well.

The XIAO is surface-mounted to the hat, which allows the BATT+ pad to be
connected as well as making for a lower-profile assembly.

A solder jumper is provided to select which power source is used for the VIK 5V
pin. By default this pin is connected to the BATT+ pad on the XIAO. The
connection can be changed to the USB 5V pin by severing the default jumper and
soldering the other.

## Fabrication and BOM

For PCB fabrication, you can use the files in the `production` folder.

* `xiao-hat.zip` - the file used to fabricate the pcb
* `bom.csv` - used for PCBA. You can also use the part numbers in this file to look up the exact parts as [lcsc.com](https://lcsc.com)
* `positions.csv` - used for PCBA

Using the 3 files above, this has been tested at [jlcpcb.com](https://jlcpcb.com)
These files were generated by the [KiCAD JLCPCB tools plugin](https://github.com/Bouni/kicad-jlcpcb-tools).

## VIK module certification

| Category                | Classification          | Response           |
| ----------------------- | ----------------------- | ------------------ |
| FPC connector           | Required                | :heavy_check_mark: |
| Breakout pins           | Recommended             | :x:                |
| Uses: SPI               | Optional                | :x:                |
| SPI used for SPI only   | Strongly recommended    | :x:                |
| Uses: I2C               | Optional                | :x:                |
| I2C used for I2C only   | Strongly Recommended    | :x:                |
| I2C pull ups            | Required                | :x:                |
| Uses: RGB               | Optional                | :x:                |
| Uses: Extra GPIO 1      | Optional                | :x:                |
| Uses: Extra GPIO 2      | Optional                | :x:                |
| Standard PCB Size/Mount | Strongly recommended    | :x:                |

## PCB images

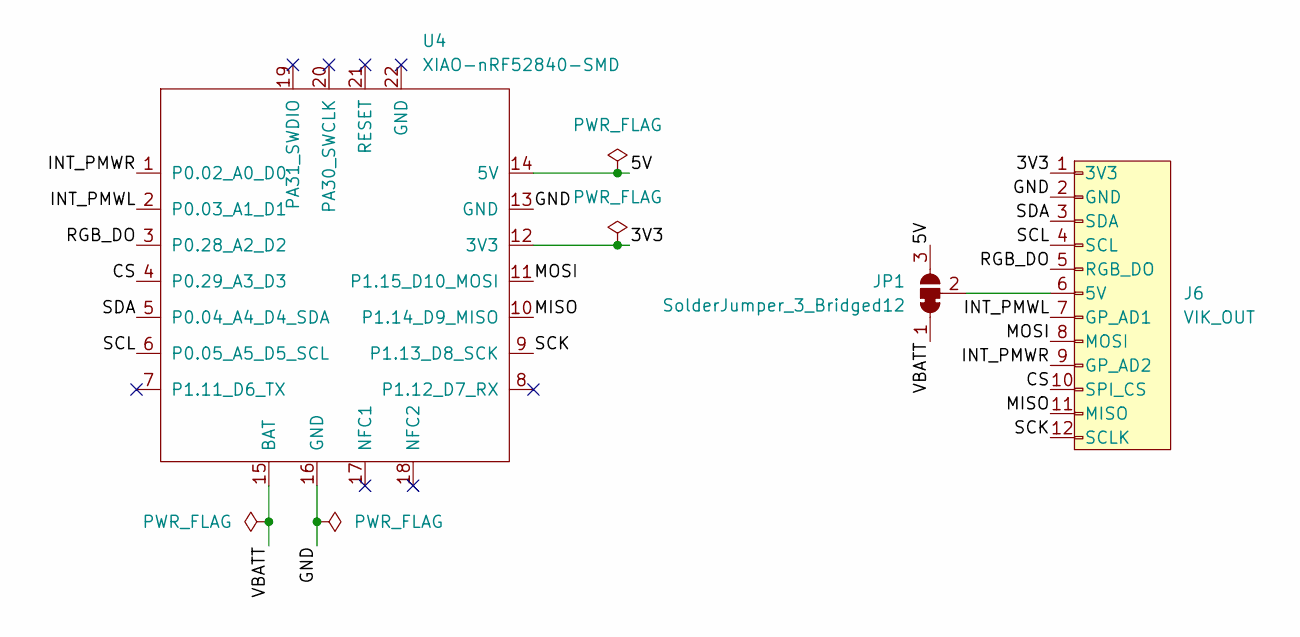
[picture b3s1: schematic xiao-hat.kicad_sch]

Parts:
J6: VIK_OUT; vik-keyboard-connector-horizontal
JP1: SolderJumper_3_Bridged12; SolderJumper-3_P1.3mm_Bridged12_RoundedPad1.0x1.5mm
U4: XIAO-nRF52840-SMD

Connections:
/3V3: J6.1 (3V3), U4.12 (3V3)
/5V: JP1.3 (B), U4.14 (5V)
/CS: J6.10 (SPI_CS), U4.4 (P0.29_A3_D3)
/GND: J6.2 (GND), U4.13 (GND), U4.16 (GND)
/INT_PMWL: J6.7 (GP_AD1), U4.2 (P0.03_A1_D1)
/INT_PMWR: J6.9 (GP_AD2), U4.1 (P0.02_A0_D0)
/MISO: J6.11 (MISO), U4.10 (P1.14_D9_MISO)
/MOSI: J6.8 (MOSI), U4.11 (P1.15_D10_MOSI)
/RGB_DO: J6.5 (RGB_DO), U4.3 (P0.28_A2_D2)
/SCK: J6.12 (SCLK), U4.9 (P1.13_D8_SCK)
/SCL: J6.4 (SCL), U4.6 (P0.05_A5_D5_SCL)
/SDA: J6.3 (SDA), U4.5 (P0.04_A4_D4_SDA)
/VBATT: JP1.1 (A), U4.15 (BAT)
unnamed: J6.6 (5V), JP1.2 (C)

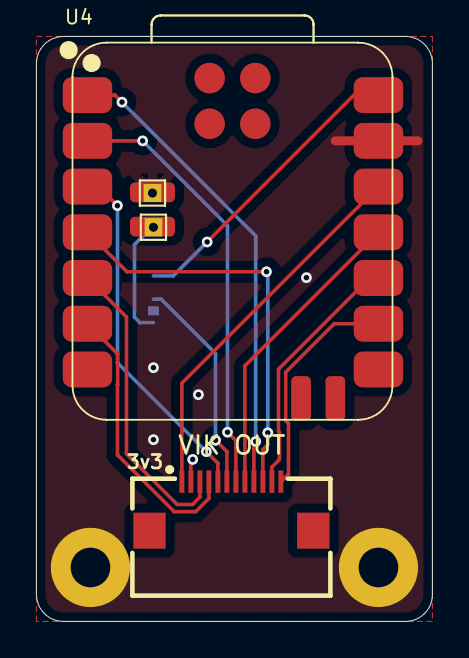
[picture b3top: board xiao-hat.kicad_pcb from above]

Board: 2 copper layers, 22.0 x 32.5 mm, 3 parts (1 on the bottom side), 14 nets.

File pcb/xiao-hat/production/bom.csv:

Designator,Footprint,Quantity,Value,LCSC Part #
J6,vik-keyboard-connector-horizontal,1,VIK_OUT,
U4,XIAO-nRF52840-SMD,1,XIAO-nRF52840-SMD,

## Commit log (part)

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2025-12-13 Create VIK-compliant version of the PMW3610-xxs module.
2025-12-13 Create a pair of modules for adapting the VIK bus to magnetic pogo pin connectors.
2025-12-13 Create a PCB for adding a VIK keyboard connector to a Seeed XIAO microcontroller.
2025-12-18 Add xiao-hat module files.
2025-12-18 Add magnetic-connector module files.
2026-01-01 Create narrow PMW3610 module.
2026-01-02 Add more dimensions to pmw3610-xxs-compliant-narrow PCB.
2026-01-09 Add more dimensions to magnetic connector PCB.
2026-02-13 Update documentation: - Rename `5V` pin to `Vout`. - Provide guidelines for use of `Vout` pin on wireless keyboards.
2026-02-13 Rename CS to GPIO/CS 3; rename GPIO 1 and 2 to GPIO/CS 1 and 2.
2026-05-18 Make magnetic connector size compliant with VIK small form factor.
2026-05-18 Make PMW-3610-narrow module compliant with VIK small form factor.
2026-05-21 Add ESD protection to magnetic connector module.
2026-05-23 Change VIK connector and ESD protection chips.
2026-05-23 Change VIK connector on trackball sensor module.
